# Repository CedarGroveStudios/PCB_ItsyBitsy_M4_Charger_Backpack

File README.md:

### _A stacking breadboard adapter for the ItsyBitsy M4 Express_

# ItsyBitsy M4 Charger Backpack

## Overview
The ItsyBitsy M4 Charger Backpack is an Adafruit ItsyBitsy M4 Express-compatible piggyback module that converts the 3-sided pinout of the ItsyBitsy to dual in-line for use on typical solderless breadboards and soldered protoboards. The adapter was also designed with extra solderable pin connections.

Included is a STEMMA-QT connector that can be optionally configured via solder jumpers to connect to the ItsyBitsy's UART (RX/TX) or I2C (SCL/SDA) signals. A 2-pin JST LiPo battery connection is on-board that supports charging (100mA charge rate), compatible with Adafruit's standard battery connector polarity. A solder jumper is also provided to optionally connect the battery monitor voltage divider to pin A6.

ItsyBitsy Breadboard Adapter [Schematic](https://github.com/CedarGroveStudios/PCB_ItsyBitsy_M4_Charger_Backpack/blob/main//PCB/ItsyBitsy%20breadboard.pdf)

OSH Park shared project: <a href="https://oshpark.com/shared_projects/MSAKdkxL"></img></a>

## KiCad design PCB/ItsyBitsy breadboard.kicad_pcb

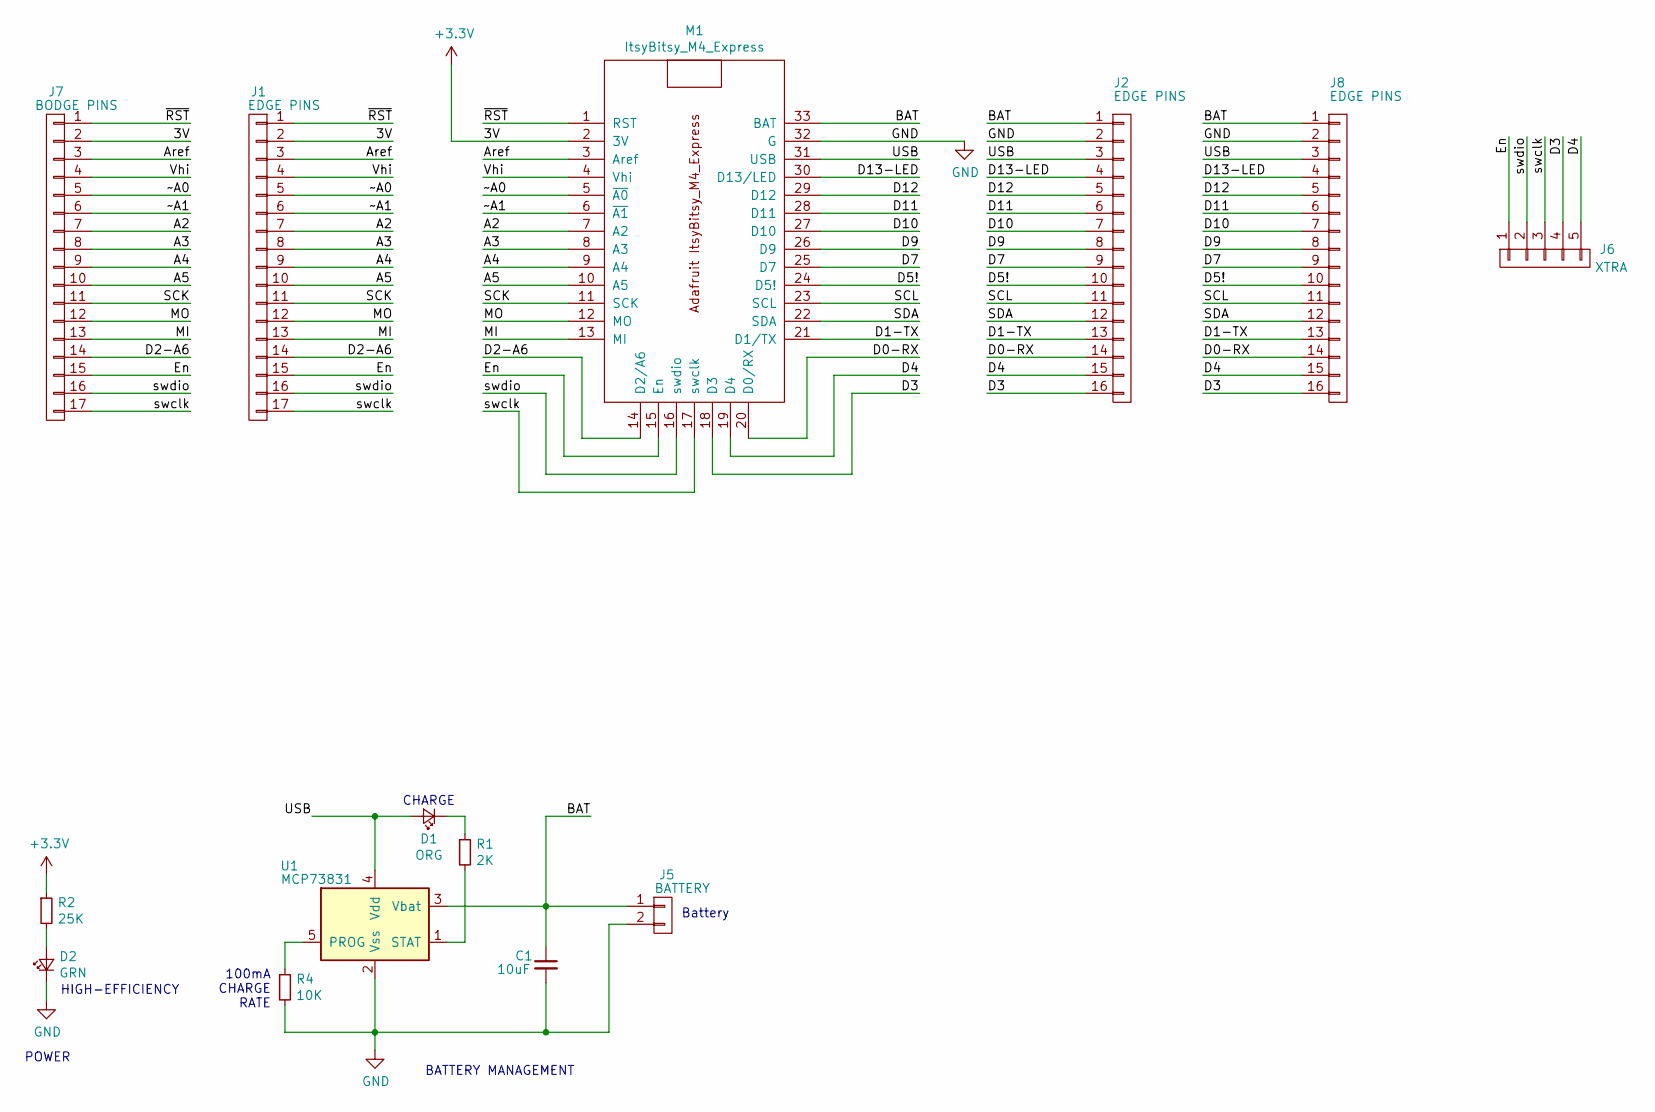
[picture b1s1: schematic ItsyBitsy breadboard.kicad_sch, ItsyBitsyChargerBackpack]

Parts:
C1: 10uF; C_0805_2012Metric
D1: ORG; LED_0805_2012Metric
D2: GRN; LED_0805_2012Metric
J1: EDGE PINS; Pin_Header_Straight_1x17_Pitch2.54mm_no_silk
J2, J8: EDGE PINS; Pin_Header_Straight_1x16_Pitch2.54mm_no_silk
J5: BATTERY; JST_PH_S2B-PH-SM4-TB_1x02-1MP_P2.00mm_Horizontal
J6: XTRA; Pin_Header_Straight_1x05_Pitch2.54mm_no_silk
J7: BODGE PINS; Pin_Header_Straight_1x17_Pitch2.54mm_no_silk
M1: ItsyBitsy_M4_Express
R1: 2K; R_0805_2012Metric
R2: 25K; R_0805_2012Metric
R4: 10K; R_0805_2012Metric
U1: MCP73831; SOT-23-5

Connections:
+3V3: J1.2, J7.2, M1.2 (3V), R2.1
/A2: J1.7, J7.7, M1.7 (A2)
/A3: J1.8, J7.8, M1.8 (A3)
/A4: J1.9, J7.9, M1.9 (A4)
/A5: J1.10, J7.10, M1.10 (A5)
/Aref: J1.3, J7.3, M1.3 (Aref)
/BAT: C1.1, J2.1, J5.1, J8.1, M1.33 (BAT), U1.3 (Vbat)
/D0-RX: J2.14, J8.14, M1.20 (D0/RX)
/D1-TX: J2.13, J8.13, M1.21 (D1/TX)
/D2-A6: J1.14, J7.14, M1.14 (D2/A6)
/D3: J2.16, J6.4, J8.16, M1.18 (D3)
/D4: J2.15, J6.5, J8.15, M1.19 (D4)
/D5!: J2.10, J8.10, M1.24 (D5!)
/D7: J2.9, J8.9, M1.25 (D7)
/D9: J2.8, J8.8, M1.26 (D9)
/D10: J2.7, J8.7, M1.27 (D10)
/D11: J2.6, J8.6, M1.28 (D11)
/D12: J2.5, J8.5, M1.29 (D12)
/D13-LED: J2.4, J8.4, M1.30 (D13/LED)
/En: J1.15, J6.1, J7.15, M1.15 (En)
/MI: J1.13, J7.13, M1.13 (MI)
/MO: J1.12, J7.12, M1.12 (MO)
/SCK: J1.11, J7.11, M1.11 (SCK)
/SCL: J2.11, J8.11, M1.23 (SCL)
/SDA: J2.12, J8.12, M1.22 (SDA)
/USB: D1.2 (A), J2.3, J8.3, M1.31 (USB), U1.4 (Vdd)
/Vhi: J1.4, J7.4, M1.4 (Vhi)
/swclk: J1.17, J6.3, J7.17, M1.17 (swclk)
/swdio: J1.16, J6.2, J7.16, M1.16 (swdio)
/~A0: J1.5, J7.5, M1.5 (~A0)
/~A1: J1.6, J7.6, M1.6 (~A1)
/~RST: J1.1, J7.1, M1.1 (RST)
GND: C1.2, D2.1 (K), J2.2, J5.2, J8.2, M1.32 (G), R4.2, U1.2 (Vss)
unnamed: D1.1 (K), R1.1
unnamed: D2.2 (A), R2.2
unnamed: R1.2, U1.1 (STAT)
unnamed: R4.1, U1.5 (PROG)

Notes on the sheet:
BATTERY MANAGEMENT
CHARGE
Battery
HIGH-EFFICIENCY
POWER
100mA CHARGE RATE

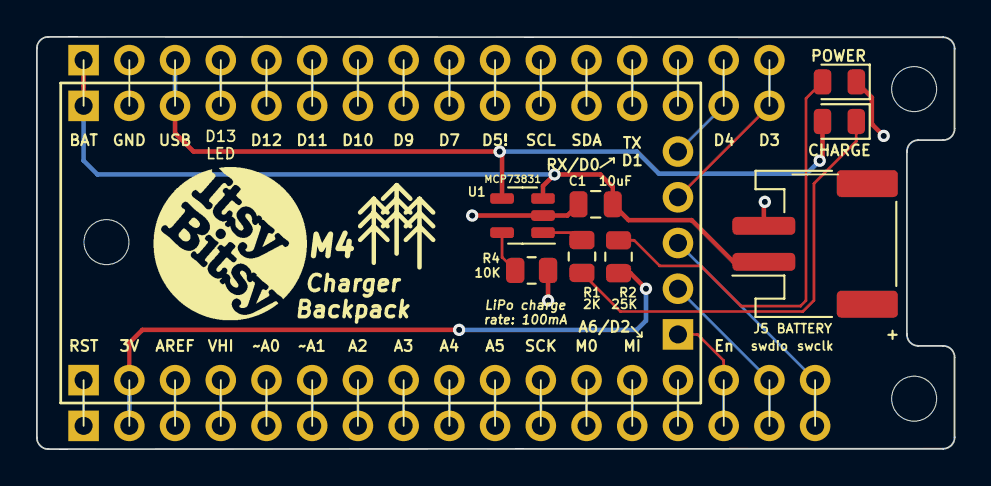
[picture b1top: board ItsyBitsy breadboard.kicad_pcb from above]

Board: 2 copper layers, 51.0 x 22.9 mm, 15 parts (1 on the bottom side), 37 nets.

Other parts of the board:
logo: ItsyBitsy_logo
logo#2: ItsyBitsy_logo

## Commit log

2023-05-31 intial repo load
2023-06-01 initial repo load
2023-06-02 update kicad backup
